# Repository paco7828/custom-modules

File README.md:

Custom made modules having the same logic and functionalities as the original modules but in more compact sizes and shapes.
Included modules:
 - battery charger
 - battery level indicator
 - breadboard
 - data-port-extender
 - dual-motor-driver
 - IR transmitter & receiver
 - step up converter (5V) using MCP1624
 - step up converter (5V) using MT3608
 - rtc module using PCF8563
 - rtc module using DS3231M
 - single relay module
 - IR proximity sensor

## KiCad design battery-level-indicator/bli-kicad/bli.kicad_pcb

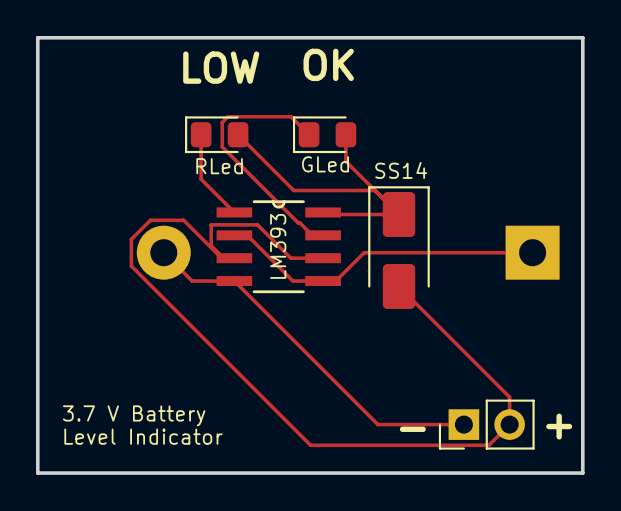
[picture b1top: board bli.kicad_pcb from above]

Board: 2 copper layers, 30.3 x 24.2 mm, 6 parts (1 on the bottom side), 6 nets.

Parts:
CR2032: CR2032; BatteryHolder_Keystone_103_1x20mm
GLed: LEDG; LED_0805_2012Metric_Pad1.15x1.40mm_HandSolder
J1: Input_Pins; PinHeader_1x02_P2.54mm_Vertical
LM393: LM393D; D8
RLed: LEDR; LED_0805_2012Metric_Pad1.15x1.40mm_HandSolder
SS14: SS14; D_SMA

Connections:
unnamed: CR2032.1 (+), LM393.2 (1IN-), LM393.5 (2IN+)
unnamed: CR2032.2 (-), J1.1, LM393.4 (GND)
unnamed: GLed.2 (A), LM393.8 (VCC), RLed.2 (A), SS14.1 (K)
unnamed: LM393.1 (1OUT), RLed.1 (K)
unnamed: GLed.1 (K), LM393.7 (2OUT)
unnamed: J1.2, LM393.3 (1IN+), LM393.6 (2IN-), SS14.2 (A)

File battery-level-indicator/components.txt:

-Battery monitoring IC - LM393D - https://www.hestore.hu/prod_10021934.html
-Output leds:
    -Red - EVL-SMD0805-RED - https://www.hestore.hu/prod_10043215.html
    -Green - EVL-GHC-XS1T2M - https://www.hestore.hu/prod_10036384.html
-Diode - SS14 Schottky - https://www.hestore.hu/prod_10039694.html
-Coin cell battery - CR2032 - https://www.hestore.hu/prod_10001070.html
-Coin cell battery holder - BS-02-A1AJ010 - https://www.hestore.hu/prod_10045258.html
-Input pins

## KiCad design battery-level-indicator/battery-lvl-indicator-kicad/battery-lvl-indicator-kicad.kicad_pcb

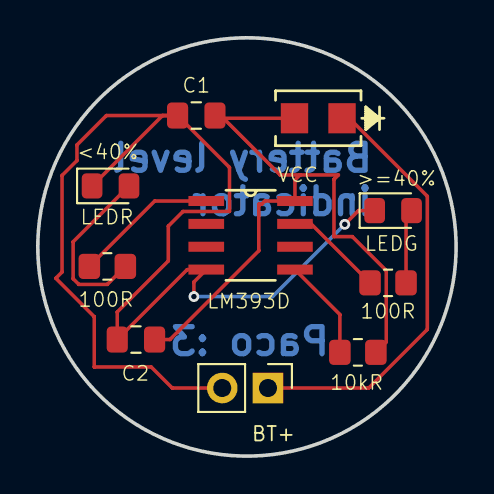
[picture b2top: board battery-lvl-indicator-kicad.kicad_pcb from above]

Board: 2 copper layers, 23.2 x 23.2 mm, 10 parts (0 on the bottom side), 8 nets.

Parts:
10kR: 10kR; R_0805_2012Metric_Pad1.20x1.40mm_HandSolder
100R, 100R#2: 100R; R_0805_2012Metric_Pad1.20x1.40mm_HandSolder
C1, C2: Capacitor; C_0805_2012Metric_Pad1.18x1.45mm_HandSolder
D1: Schottky_Diode; DO-214AC_VIS
J1: BT+; PinHeader_1x02_P2.54mm_Vertical
LEDG: LED_Green; LED_0805_2012Metric_Pad1.15x1.40mm_HandSolder
LEDR: LED_Red; LED_0805_2012Metric_Pad1.15x1.40mm_HandSolder
U1: LM393D; D8

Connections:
unnamed: 10kR.2, C1.2, C2.2, D1.2 (A), U1.8 (VCC)
unnamed: D1.1 (K), J1.1
unnamed: 100R#2.2, LEDR.2 (A)
unnamed: C1.1, C2.1, J1.2, LEDG.1 (K), LEDR.1 (K), U1.4 (GND)
unnamed: 100R.2, LEDG.2 (A)
unnamed: 100R#2.1, U1.1 (1OUT)
unnamed: 10kR.1, U1.5 (2IN+)
unnamed: 100R.1, U1.7 (2OUT)

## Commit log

2024-12-07 Added battery level indicator components.
2024-12-07 Small correction in components.txt.
2024-12-07 Changed resistors from tht to smd.
2024-12-07 Added reference voltage resistors.
2024-12-07 Changed resistors to resistor.
2024-12-07 Added demo circuit plan.
2024-12-08 Added KiCad prototype pcb, no connections.
2024-12-08 Added connections to pcb.
2024-12-09 Collected the components and planned the circuit for the RTC module.
2024-12-09 Created the schema and added footprints for the circuit in kicad.
2024-12-09 PCB done without connections.
2024-12-09 Connected items on the pcb.
2024-12-10 Added the gerber and drill files ready to order!
2024-12-19 Temp save for components
2024-12-19 Finished the components for the boost converter.
2024-12-19 Added boost converters IC's pinout as image.
2024-12-22 Added demo circuit plan of the boost converter and an internal reference voltage stabilizator 100nF capacitor to the components list.
2024-12-24 Removed previous PCB, project startover.
2024-12-24 Added new proto.
2024-12-25 Modified components at battery level indicator.
2024-12-25 Updated normal battery level indicator proto with diode.
2024-12-25 Finished with the final PCB of the battery level indicator.
2024-12-25 Updated components at the boost converter.
2024-12-25 Updated the boost converter new demo circuit.
2024-12-25 Added futute features of custom microcontroller.
2024-12-26 Added minimum config image for a microcontroller
2025-01-15 Removed diodes from the rtc module.
2025-01-16 Added the PCF8563 self-made library.
2025-03-27 Added new functions.
2025-03-27 Added function to retrieve seconds.
2025-05-19 Removed unused files, added pcb gerber files..
2025-05-19 Removed unnecessary files and added rtc pcb.
2025-05-19 Changed mcp1624 pcb.
2025-05-19 Changed data port extender pcb.
2025-05-19 Renamed rtc folder and added ir tx rx pcb.
2025-05-19 Added battery charger module pcb.
2025-05-19 Adjusted step up pcb.
2025-05-30 Added rtc and step up module showcase images.
2025-06-04 Added pcb images of IR-Tx-Rx.
2025-06-04 Added images of battery charger pcb.
2025-06-04 Added protection diodes and p-mosfets to inputs.
2025-06-07 Added new module called multicell tp4056 charger.
2025-06-07 Added new module, dual h bridge. Added protection against reverse polarity at charger module.
2025-06-07 Added V2 IR-Tx-Rx and component list.
2025-06-07 Added protection diodes and components list to step up module 5V.
2025-06-07 Added protection diode to PCF8563 RTC module and components list.
2025-06-07 Added components list to multicell-tp4056-charger.
2025-06-07 Added components list to battery charger module.
2025-06-11 Created components list and added V1 pcb for IR distance sensor.
2025-06-11 Renamed step up converter with output voltage included in folder name.
2025-06-14 Removed led and resistor from pcf8563 rtc module.
2025-06-14 Sorted RTC folder into 2 separate rtc modules. Added components and PCBs.
2025-06-18 Removed a schottky diode due to its unnecessarity.
2025-07-30 Removed IR distance sensor due to being faulty.
2025-07-30 Removed multicell tp4056 charger due to being faulty.
2025-07-30 Renamed step up converter to IC-name followed by original name.
2025-07-30 Added new step up converter module using the mt3608 IC.
2025-07-30 Added custom breadboard alongside with components list.
2025-07-30 Renamed mt3608 step up converter module to V1.
2025-07-30 Added single relay module with its component and pcb.
2025-08-01 Added IR proximity sensor module.
2025-08-01 Update README.md with IR proximity sensor
2025-08-18 Updated mt3608 5v step up converter component list and pcb with new 22uH inductor instead of 10uH.
2025-08-22 Added powerbank components.
2025-08-22 Added power bank 5v PCB.
2025-08-23 Moved vias from direct smd pads in powerbank-5v pcb.
2025-09-20 Added components list and PCB for battery-ready module V1.
2025-10-30 Added V1 shell for 5V powerbank
2025-11-02 Added correcter 5v powerbank shell.
2025-11-03 Modified 5v powerbank 3D shell's wall from 2mm to 1.5mm.
2025-11-06 Adjusted powerbank-5v-shell gaps.
